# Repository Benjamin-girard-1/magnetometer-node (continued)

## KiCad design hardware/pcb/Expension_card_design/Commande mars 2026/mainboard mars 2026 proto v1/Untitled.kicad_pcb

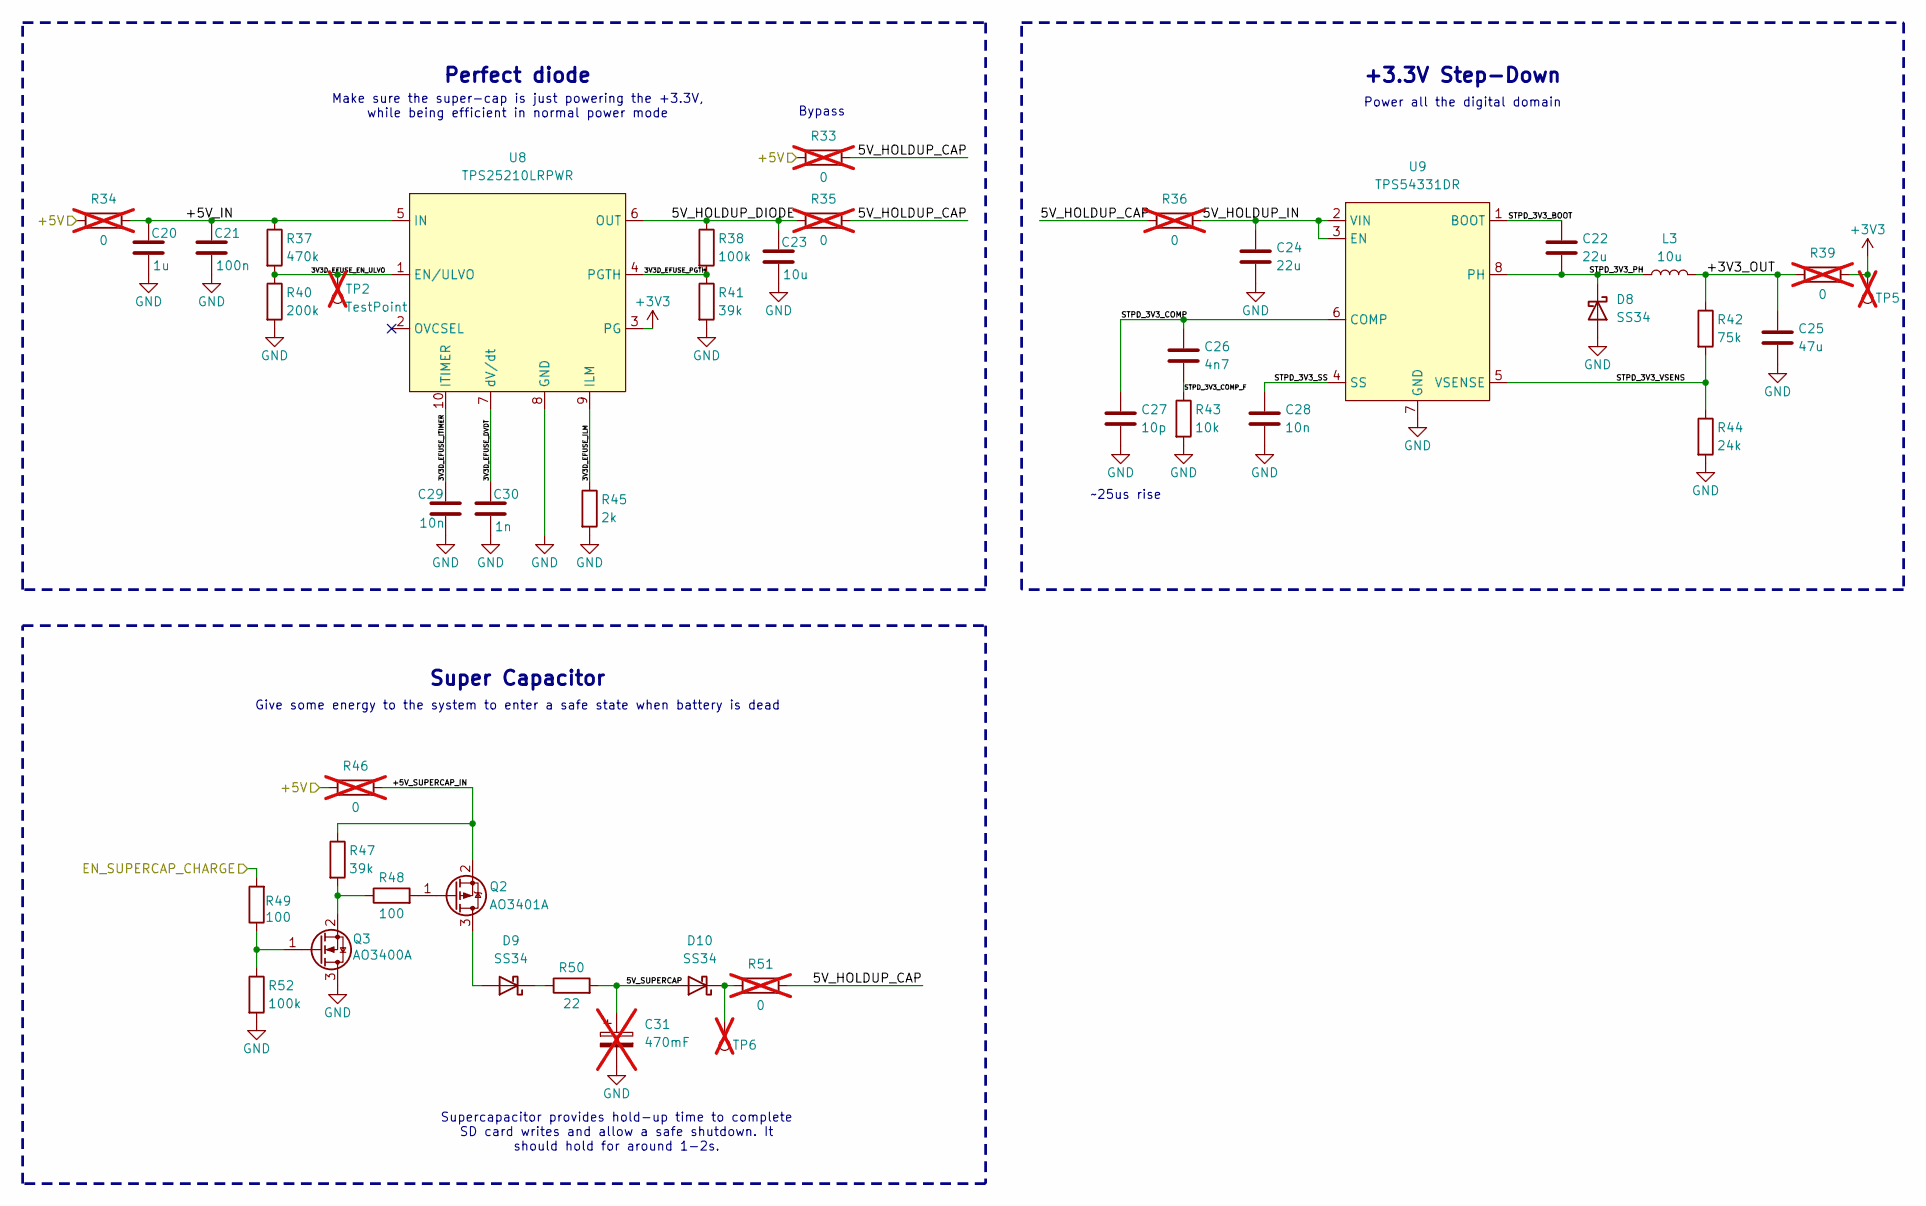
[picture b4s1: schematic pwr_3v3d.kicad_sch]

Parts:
C20: 1u; C_0805_2012Metric; LCSC C28323
C21: 100n; C_0603_1608Metric; LCSC C14663
C22, C24: 22u; C_1206_3216Metric; LCSC C12891
C23: 10u; C_0805_2012Metric; LCSC C15850
C25: 47u; C_1206_3216Metric; LCSC C96123
C26: 4n7; C_0603_1608Metric; LCSC C53987
C27: 10p; C_0603_1608Metric; LCSC C1634
C28, C29: 10n; C_0603_1608Metric; LCSC C57112
C30: 1n; C_0603_1608Metric; LCSC C1588
C31: 470mF; C_Radial_D8.0mm_P11.50mm; not fitted
D8, D9, D10: SS34; D_SMA; LCSC C8678
L3: 10u; L_Sunlord_MWSA0503S; LCSC C177248
Q2: AO3401A; SOT-23; LCSC C15127
Q3: AO3400A; SOT-23; LCSC C20917
R33, R34, R35, R36, R39, R46, R51: 0; R_1206_3216Metric; LCSC C17888; not fitted
R37: 470k; R_0603_1608Metric; LCSC C23178
R38, R52: 100k; R_0603_1608Metric; LCSC C25803
R40: 200k; R_0603_1608Metric; LCSC C25811
R41, R47: 39k; R_0603_1608Metric; LCSC C23153
R42: 75k; R_0603_1608Metric; LCSC C23242
R43: 10k; R_0603_1608Metric; LCSC C25804
R44: 24k; R_0603_1608Metric; LCSC C23352
R45: 2k; R_0603_1608Metric; LCSC C22975
R48, R49: 100; R_0603_1608Metric; LCSC C22775
R50: 22; R_2512_6332Metric; LCSC C2974113
TP2, TP5, TP6: TestPoint; TestPoint_THTPad_1.0x1.0mm_Drill0.5mm; not fitted
U8: TPS25210LRPWR; SMD_VQFN-HR-10; LCSC C2861226
U9: TPS54331DR; SOIC-8_3.9x4.9mm_P1.27mm; LCSC C9865

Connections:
+3V3: R39.2, TP5.1, U8.3 (PG); also elsewhere on the board
+5V: R33.1, R34.1, R46.1; also elsewhere on the board
/MCU_ESP32S3/EN_SUPERCAP_CHARGE: R49.2; also elsewhere on the board
/PWR_3V3D/3V3D_EFUSE_DVDT: C30.1, U8.7 (dV/dt)
/PWR_3V3D/3V3D_EFUSE_EN_ULVO: R37.2, R40.1, TP2.1, U8.1 (EN/ULVO)
/PWR_3V3D/3V3D_EFUSE_ILM: R45.1, U8.9 (ILM)
/PWR_3V3D/3V3D_EFUSE_ITIMER: C29.1, U8.10 (ITIMER)
/PWR_3V3D/3V3D_EFUSE_PGTH: R38.2, R41.1, U8.4 (PGTH)
/PWR_3V3D/5V_HOLDUP_CAP: R33.2, R35.2, R36.1, R51.2
/PWR_3V3D/5V_HOLDUP_DIODE: C23.1, R35.1, R38.1, U8.6 (OUT)
/PWR_3V3D/5V_HOLDUP_IN: C24.1, R36.2, U9.2 (VIN), U9.3 (EN)
/PWR_3V3D/5V_SUPERCAP: C31.1, D10.2 (A), R50.2
/PWR_3V3D/+3V3_OUT: C25.1, L3.2, R39.1, R42.1
/PWR_3V3D/+5V_IN: C20.1, C21.1, R34.2, R37.1, U8.5 (IN)
/PWR_3V3D/+5V_SUPERCAP_IN: Q2.2 (S), R46.2, R47.1
/PWR_3V3D/STPD_3V3_BOOT: C22.1, U9.1 (BOOT)
/PWR_3V3D/STPD_3V3_COMP: C26.1, C27.1, U9.6 (COMP)
/PWR_3V3D/STPD_3V3_COMP_F: C26.2, R43.1
/PWR_3V3D/STPD_3V3_PH: C22.2, D8.1 (K), L3.1, U9.8 (PH)
/PWR_3V3D/STPD_3V3_SS: C28.1, U9.4 (SS)
/PWR_3V3D/STPD_3V3_VSENS: R42.2, R44.1, U9.5 (VSENSE)
GND: C20.2, C21.2, C23.2, C24.2, C25.2, C27.2, C28.2, C29.2, C30.2, C31.2, D8.2 (A), Q3.3 (D), R40.2, R41.2, R43.2, R44.2, R45.2, R52.2, U8.8 (GND), U9.7 (GND); also elsewhere on the board
unnamed: D9.2 (A), Q2.3 (D)
unnamed: D9.1 (K), R50.1
unnamed: D10.1 (K), R51.1, TP6.1
unnamed: Q2.1 (G), R48.2
unnamed: Q3.1 (G), R49.1, R52.1
unnamed: Q3.2 (S), R47.2, R48.1

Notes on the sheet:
Make sure the super-cap is just powering the +3.3V, while being efficient in normal power mode
~25us rise
Super Capacitor
Give some energy to the system to enter a safe state when battery is dead
+3.3V Step-Down
Power all the digital domain
Supercapacitor provides hold-up time to complete SD card writes and allow a safe shutdown. It should hold for around 1-2s.
Bypass
Perfect diode

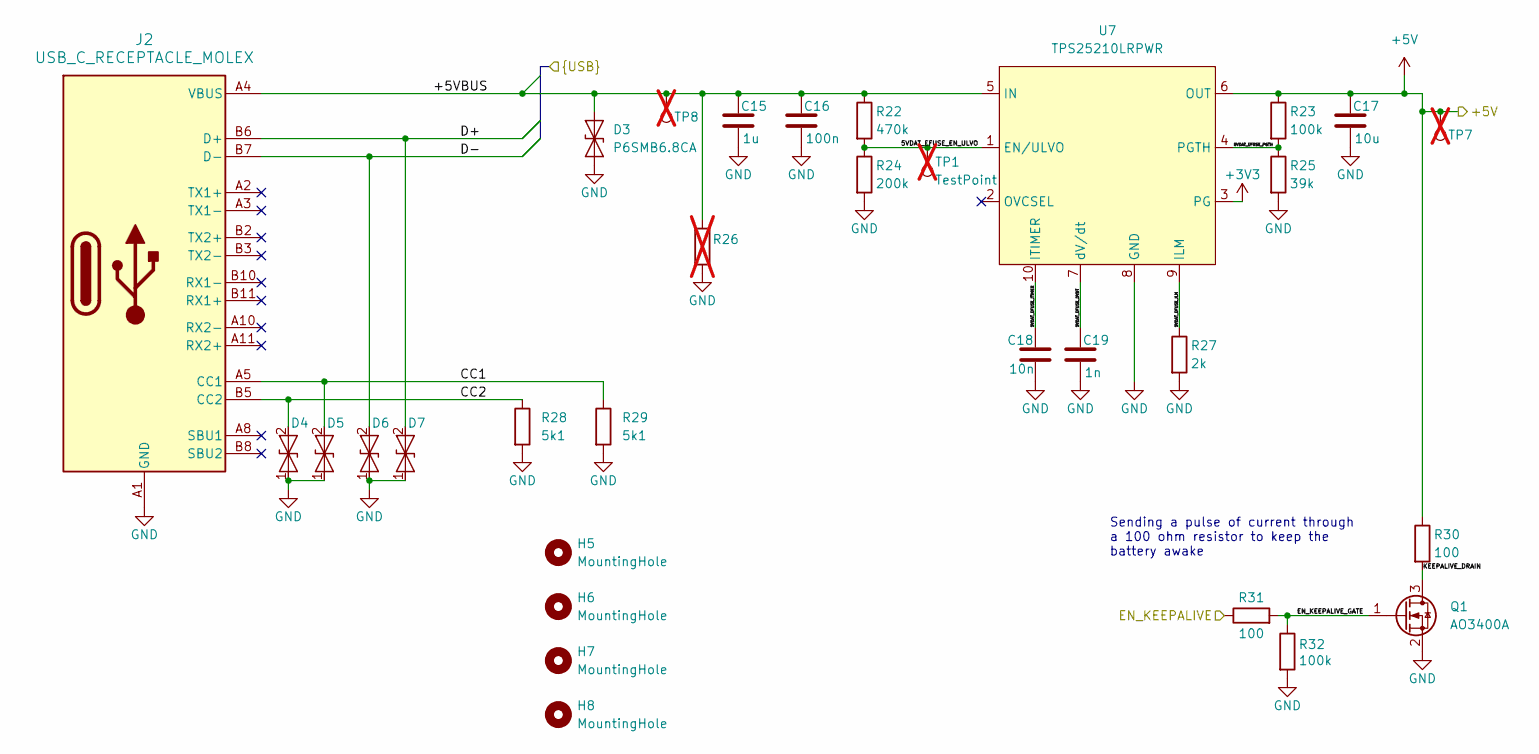
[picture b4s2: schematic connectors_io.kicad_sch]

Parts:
C15: 1u; C_0805_2012Metric; LCSC C28323
C16: 100n; C_0603_1608Metric; LCSC C14663
C17: 10u; C_0805_2012Metric; LCSC C15850
C18: 10n; C_0603_1608Metric; LCSC C57112
C19: 1n; C_0603_1608Metric; LCSC C1588
D3: P6SMB6.8CA; D_SMB; LCSC C7420377
D4, D5, D6, D7: H5VUD5BB; D_SOD-523; LCSC C20615820
H5, H6, H7, H8: MountingHole; MountingHole_4.3mm_M4
J2: USB_C_RECEPTACLE_MOLEX; CONN_201267-0005_MOL; LCSC C565324
Q1: AO3400A; SOT-23; LCSC C20917
R22: 470k; R_0603_1608Metric; LCSC C23178
R23, R32: 100k; R_0603_1608Metric; LCSC C25803
R24: 200k; R_0603_1608Metric; LCSC C25811
R25: 39k; R_0603_1608Metric; LCSC C23153
R26: R_1206_3216Metric_Pad1.30x1.75mm_HandSolder; not fitted
R27: 2k; R_0603_1608Metric; LCSC C22975
R28, R29: 5k1; R_0603_1608Metric; LCSC C23186
R30, R31: 100; R_0603_1608Metric; LCSC C22775
TP1, TP7, TP8: TestPoint; TestPoint_THTPad_1.0x1.0mm_Drill0.5mm; not fitted
U7: TPS25210LRPWR; SMD_VQFN-HR-10; LCSC C2861226

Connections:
+3V3: U7.3 (PG); also elsewhere on the board
+5V: C17.1, R23.1, R30.1, TP7.1, U7.6 (OUT); also elsewhere on the board
/DATA_SAVING/+5VBUS: C15.1, C16.1, D3.2 (A2), J2.A4 (VBUS), J2.A9 (VBUS), J2.B4 (VBUS), J2.B9 (VBUS), R22.1, R26.2, TP8.1, U7.5 (IN); also elsewhere on the board
/DATA_SAVING/CC1: D5.2, J2.A5 (CC1), R29.1
/DATA_SAVING/CC2: D4.2, J2.B5 (CC2), R28.1
/DATA_SAVING/D+: D7.2, J2.A6 (D+), J2.B6 (D+); also elsewhere on the board
/DATA_SAVING/D-: D6.2, J2.A7 (D-), J2.B7 (D-); also elsewhere on the board
/IO_CONNECTOR/5VDAT_EFUSE_DVDT: C19.1, U7.7 (dV/dt)
/IO_CONNECTOR/5VDAT_EFUSE_EN_ULVO: R22.2, R24.1, TP1.1, U7.1 (EN/ULVO)
/IO_CONNECTOR/5VDAT_EFUSE_ILM: R27.1, U7.9 (ILM)
/IO_CONNECTOR/5VDAT_EFUSE_ITIMER: C18.1, U7.10 (ITIMER)
/IO_CONNECTOR/5VDAT_EFUSE_PGTH: R23.2, R25.1, U7.4 (PGTH)
/IO_CONNECTOR/EN_KEEPALIVE: R31.1; also elsewhere on the board
/IO_CONNECTOR/EN_KEEPALIVE_GATE: Q1.1 (G), R31.2, R32.1
/IO_CONNECTOR/KEEPALIVE_DRAIN: Q1.3 (D), R30.2
GND: C15.2, C16.2, C17.2, C18.2, C19.2, D3.1 (A1), D4.1, D5.1, D6.1, D7.1, J2.A1 (GND), J2.A12 (GND), J2.B1 (GND), J2.B12 (GND), Q1.2 (S), R24.2, R25.2, R26.1, R27.2, R28.2, R29.2, R32.2, U7.8 (GND); also elsewhere on the board

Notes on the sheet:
Sending a pulse of current through a 100 ohm resistor to keep the battery awake

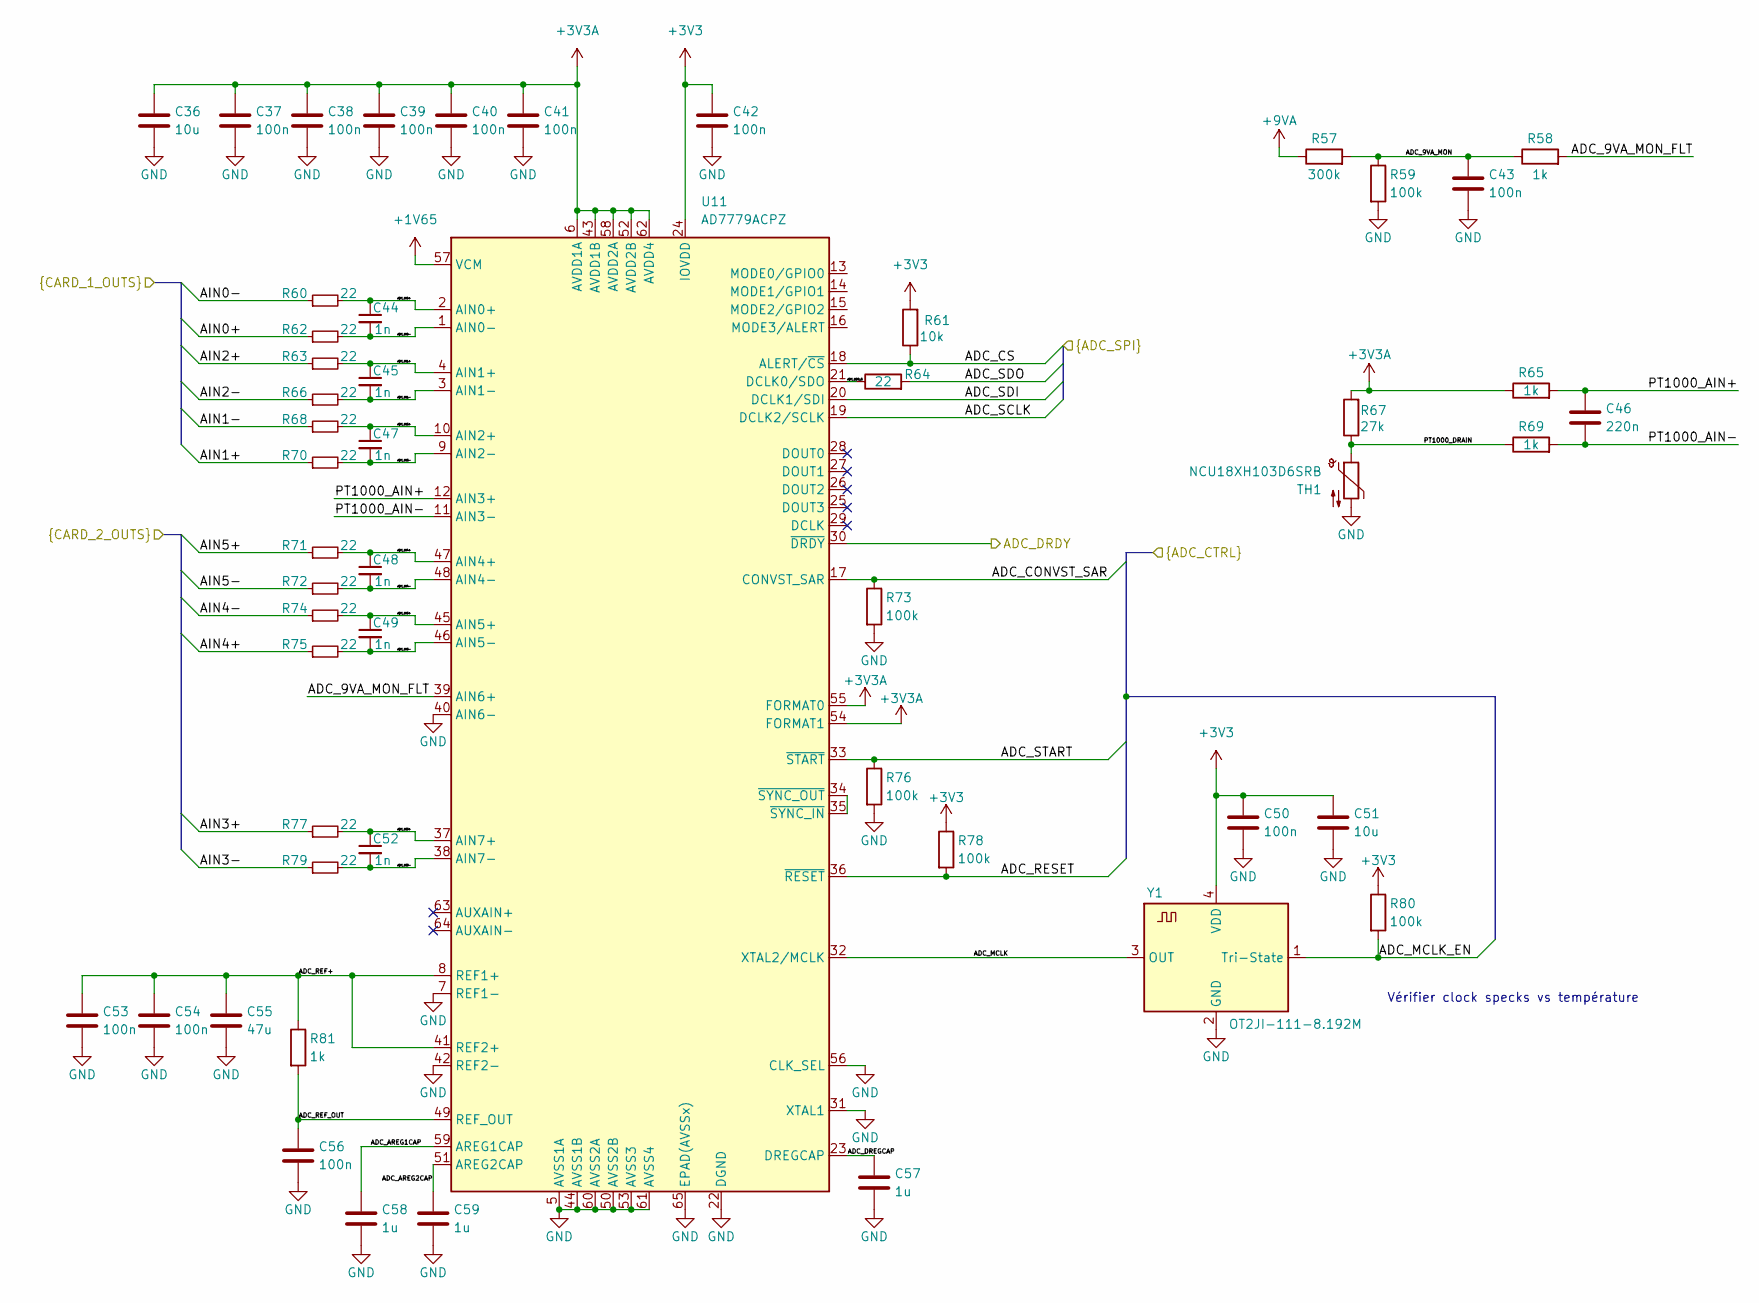
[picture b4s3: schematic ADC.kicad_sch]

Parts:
C36, C51: 10u; C_0805_2012Metric; LCSC C15850
C37, C38, C39, C40, C41, C42, C43, C50, C53, C54, C56: 100n; C_0603_1608Metric; LCSC C14663
C44, C45, C47, C48, C49, C52: 1n; C_0603_1608Metric; LCSC C1588
C46: 220n; C_0603_1608Metric; LCSC C21120
C55: 47u; C_1206_3216Metric; LCSC C96123
C57, C58, C59: 1u; C_0805_2012Metric; LCSC C28323
R57: 300k; R_0603_1608Metric; LCSC C23024
R58, R65, R69, R81: 1k; R_0603_1608Metric; LCSC C21190
R59, R73, R76, R78, R80: 100k; R_0603_1608Metric; LCSC C25803
R60, R62, R63, R64, R66, R68, R70, R71, R72, R74, R75, R77, R79: 22; R_0603_1608Metric; LCSC C23345
R61: 10k; R_0603_1608Metric; LCSC C25804
R67: 27k; R_0805_2012Metric; LCSC C17526
TH1: NCU18XH103D6SRB; R_0603_1608Metric; LCSC C3154835
U11: AD7779ACPZ; QFN-64-1EP_9x9mm_P0.5mm_EP7.65x7.65mm; LCSC C398822
Y1: OT2JI-111-8.192M; Crystal_SMD_3225-4Pin_3.2x2.5mm; LCSC C7425393

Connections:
+1V65: U11.57 (VCM); also elsewhere on the board
+3V3: C42.1, C50.1, C51.1, R61.2, R78.1, R80.1, U11.24 (IOVDD), Y1.4 (VDD); also elsewhere on the board
+3V3A: C36.1, C37.1, C38.1, C39.1, C40.1, C41.1, R65.1, R67.2, U11.6 (AVDD1A), U11.43 (AVDD1B), U11.52 (AVDD2B), U11.54 (FORMAT1), U11.55 (FORMAT0), U11.58 (AVDD2A), U11.62 (AVDD4); also elsewhere on the board
+9VA: R57.1; also elsewhere on the board
/ADC_AD777x/ADC_9VA_MON: C43.1, R57.2, R58.1, R59.1
/ADC_AD777x/ADC_9VA_MON_FLT: R58.2, U11.39 (AIN6+)
/ADC_AD777x/ADC_AREG1CAP: C58.1, U11.59 (AREG1CAP)
/ADC_AD777x/ADC_AREG2CAP: C59.1, U11.51 (AREG2CAP)
/ADC_AD777x/ADC_CONVST_SAR: R73.1, U11.17 (CONVST_SAR); also elsewhere on the board
/ADC_AD777x/ADC_CS: R61.1, U11.18 (ALERT/~CS); also elsewhere on the board
/ADC_AD777x/ADC_DRDY: U11.30 (~DRDY); also elsewhere on the board
/ADC_AD777x/ADC_DREGCAP: C57.1, U11.23 (DREGCAP)
/ADC_AD777x/ADC_IN0+: C44.1, R60.2, U11.2 (AIN0+)
/ADC_AD777x/ADC_IN0-: C44.2, R62.2, U11.1 (AIN0-)
/ADC_AD777x/ADC_IN1+: C45.1, R63.2, U11.4 (AIN1+)
/ADC_AD777x/ADC_IN1-: C45.2, R66.2, U11.3 (AIN1-)
/ADC_AD777x/ADC_IN2+: C47.1, R68.2, U11.10 (AIN2+)
/ADC_AD777x/ADC_IN2-: C47.2, R70.2, U11.9 (AIN2-)
/ADC_AD777x/ADC_IN3+: C52.1, R77.2, U11.37 (AIN7+)
/ADC_AD777x/ADC_IN3-: C52.2, R79.2, U11.38 (AIN7-)
/ADC_AD777x/ADC_IN4+: C48.1, R71.2, U11.47 (AIN4+)
/ADC_AD777x/ADC_IN4-: C48.2, R72.2, U11.48 (AIN4-)
/ADC_AD777x/ADC_IN5+: C49.1, R74.2, U11.45 (AIN5+)
/ADC_AD777x/ADC_IN5-: C49.2, R75.2, U11.46 (AIN5-)
/ADC_AD777x/ADC_MCLK: U11.32 (XTAL2/MCLK), Y1.3 (OUT)
/ADC_AD777x/ADC_MCLK_EN: R80.2, Y1.1 (Tri-State); also elsewhere on the board
/ADC_AD777x/ADC_REF+: C53.1, C54.1, C55.1, R81.1, U11.8 (REF1+), U11.41 (REF2+)
/ADC_AD777x/ADC_REF_OUT: C56.1, R81.2, U11.49 (REF_OUT)
/ADC_AD777x/ADC_RESET: R78.2, U11.36 (~RESET); also elsewhere on the board
/ADC_AD777x/ADC_SCLK: U11.19 (DCLK2/SCLK); also elsewhere on the board
/ADC_AD777x/ADC_SDI: U11.20 (DCLK1/SDI); also elsewhere on the board
/ADC_AD777x/ADC_SDO: R64.2; also elsewhere on the board
/ADC_AD777x/ADC_SDO_R: R64.1, U11.21 (DCLK0/SDO)
/ADC_AD777x/ADC_START: R76.1, U11.33 (~START); also elsewhere on the board
/ADC_AD777x/AIN0+: R62.1; also elsewhere on the board
/ADC_AD777x/AIN0-: R60.1; also elsewhere on the board
/ADC_AD777x/AIN1+: R70.1; also elsewhere on the board
/ADC_AD777x/AIN1-: R68.1; also elsewhere on the board
/ADC_AD777x/AIN2+: R63.1; also elsewhere on the board
/ADC_AD777x/AIN2-: R66.1; also elsewhere on the board
/ADC_AD777x/AIN3+: R77.1; also elsewhere on the board
/ADC_AD777x/AIN3-: R79.1; also elsewhere on the board
/ADC_AD777x/AIN4+: R75.1; also elsewhere on the board
/ADC_AD777x/AIN4-: R74.1; also elsewhere on the board
/ADC_AD777x/AIN5+: R71.1; also elsewhere on the board
/ADC_AD777x/AIN5-: R72.1; also elsewhere on the board
/ADC_AD777x/PT1000_AIN+: C46.1, R65.2, U11.12 (AIN3+)
/ADC_AD777x/PT1000_AIN-: C46.2, R69.2, U11.11 (AIN3-)
/ADC_AD777x/PT1000_DRAIN: R67.1, R69.1, TH1.1
GND: C36.2, C37.2, C38.2, C39.2, C40.2, C41.2, C42.2, C43.2, C50.2, C51.2, C53.2, C54.2, C55.2, C56.2, C57.2, C58.2, C59.2, R59.2, R73.2, R76.2, TH1.2, U11.5 (AVSS1A), U11.7 (REF1-), U11.22 (DGND), U11.31 (XTAL1), U11.40 (AIN6-), U11.42 (REF2-), U11.44 (AVSS1B), U11.50 (AVSS2B), U11.53 (AVSS3), U11.56 (CLK_SEL), U11.60 (AVSS2A), U11.61 (AVSS4), U11.65 (EPAD(AVSSx)), Y1.2 (GND); also elsewhere on the board
unnamed: U11.34 (~SYNC_OUT), U11.35 (~SYNC_IN)

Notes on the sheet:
Vérifier clock specks vs température

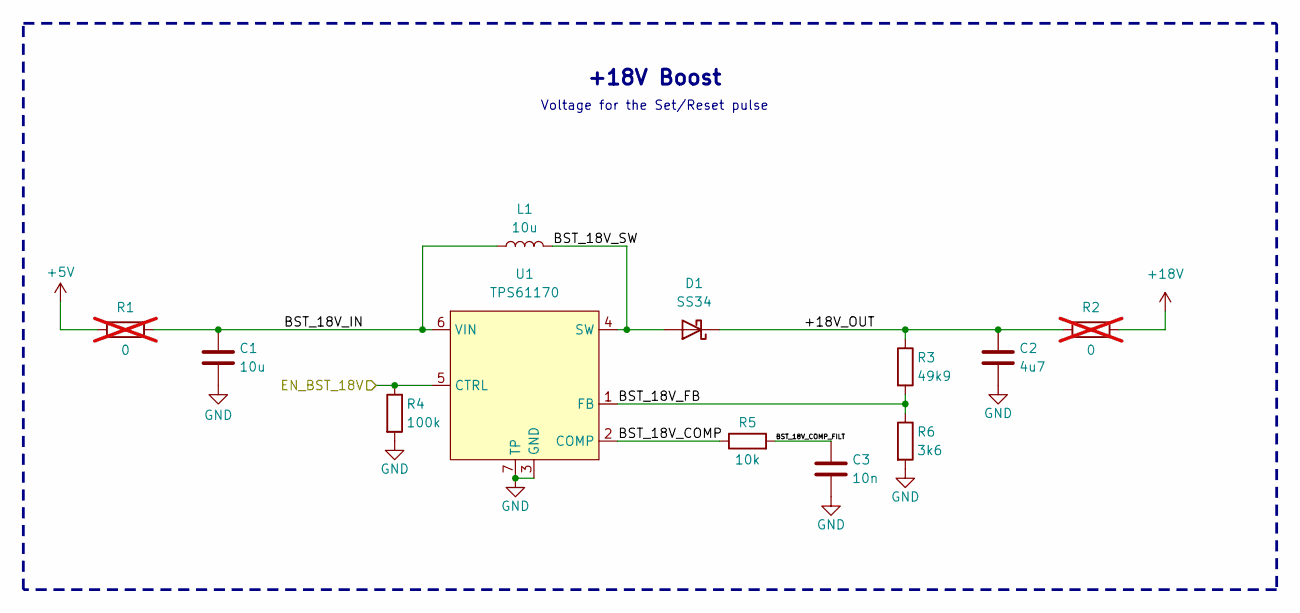
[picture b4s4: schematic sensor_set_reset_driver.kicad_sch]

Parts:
C1: 10u; C_0805_2012Metric; LCSC C15850
C2: 4u7; C_1206_3216Metric; LCSC C29823
C3: 10n; C_0603_1608Metric; LCSC C57112
D1: SS34; D_SMA; LCSC C8678
L1: 10u; L_Sunlord_MWSA0503S; LCSC C177248
R1, R2: 0; R_1206_3216Metric; LCSC C17888; not fitted
R3: 49k9; R_0603_1608Metric; LCSC C23184
R4: 100k; R_0603_1608Metric; LCSC C25803
R5: 10k; R_0603_1608Metric; LCSC C25804
R6: 3k6; R_0603_1608Metric; LCSC C22980
U1: TPS61170; WSON-6-1EP_2x2mm_P0.65mm_EP1x1.6mm; LCSC C15163

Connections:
+5V: R1.1; also elsewhere on the board
+18V: R2.2; also elsewhere on the board
/MCU_ESP32S3/EN_BST_18V: R4.1, U1.5 (CTRL); also elsewhere on the board
/SENSOR_SET_RESET_DRIVER/+18V_OUT: C2.1, D1.1 (K), R2.1, R3.1
/SENSOR_SET_RESET_DRIVER/BST_18V_COMP: R5.1, U1.2 (COMP)
/SENSOR_SET_RESET_DRIVER/BST_18V_COMP_FILT: C3.1, R5.2
/SENSOR_SET_RESET_DRIVER/BST_18V_FB: R3.2, R6.1, U1.1 (FB)
/SENSOR_SET_RESET_DRIVER/BST_18V_IN: C1.1, L1.1, R1.2, U1.6 (VIN)
/SENSOR_SET_RESET_DRIVER/BST_18V_SW: D1.2 (A), L1.2, U1.4 (SW)
GND: C1.2, C2.2, C3.2, R4.2, R6.2, U1.3 (GND), U1.7 (TP); also elsewhere on the board

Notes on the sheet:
+18V Boost
Voltage for the Set/Reset pulse

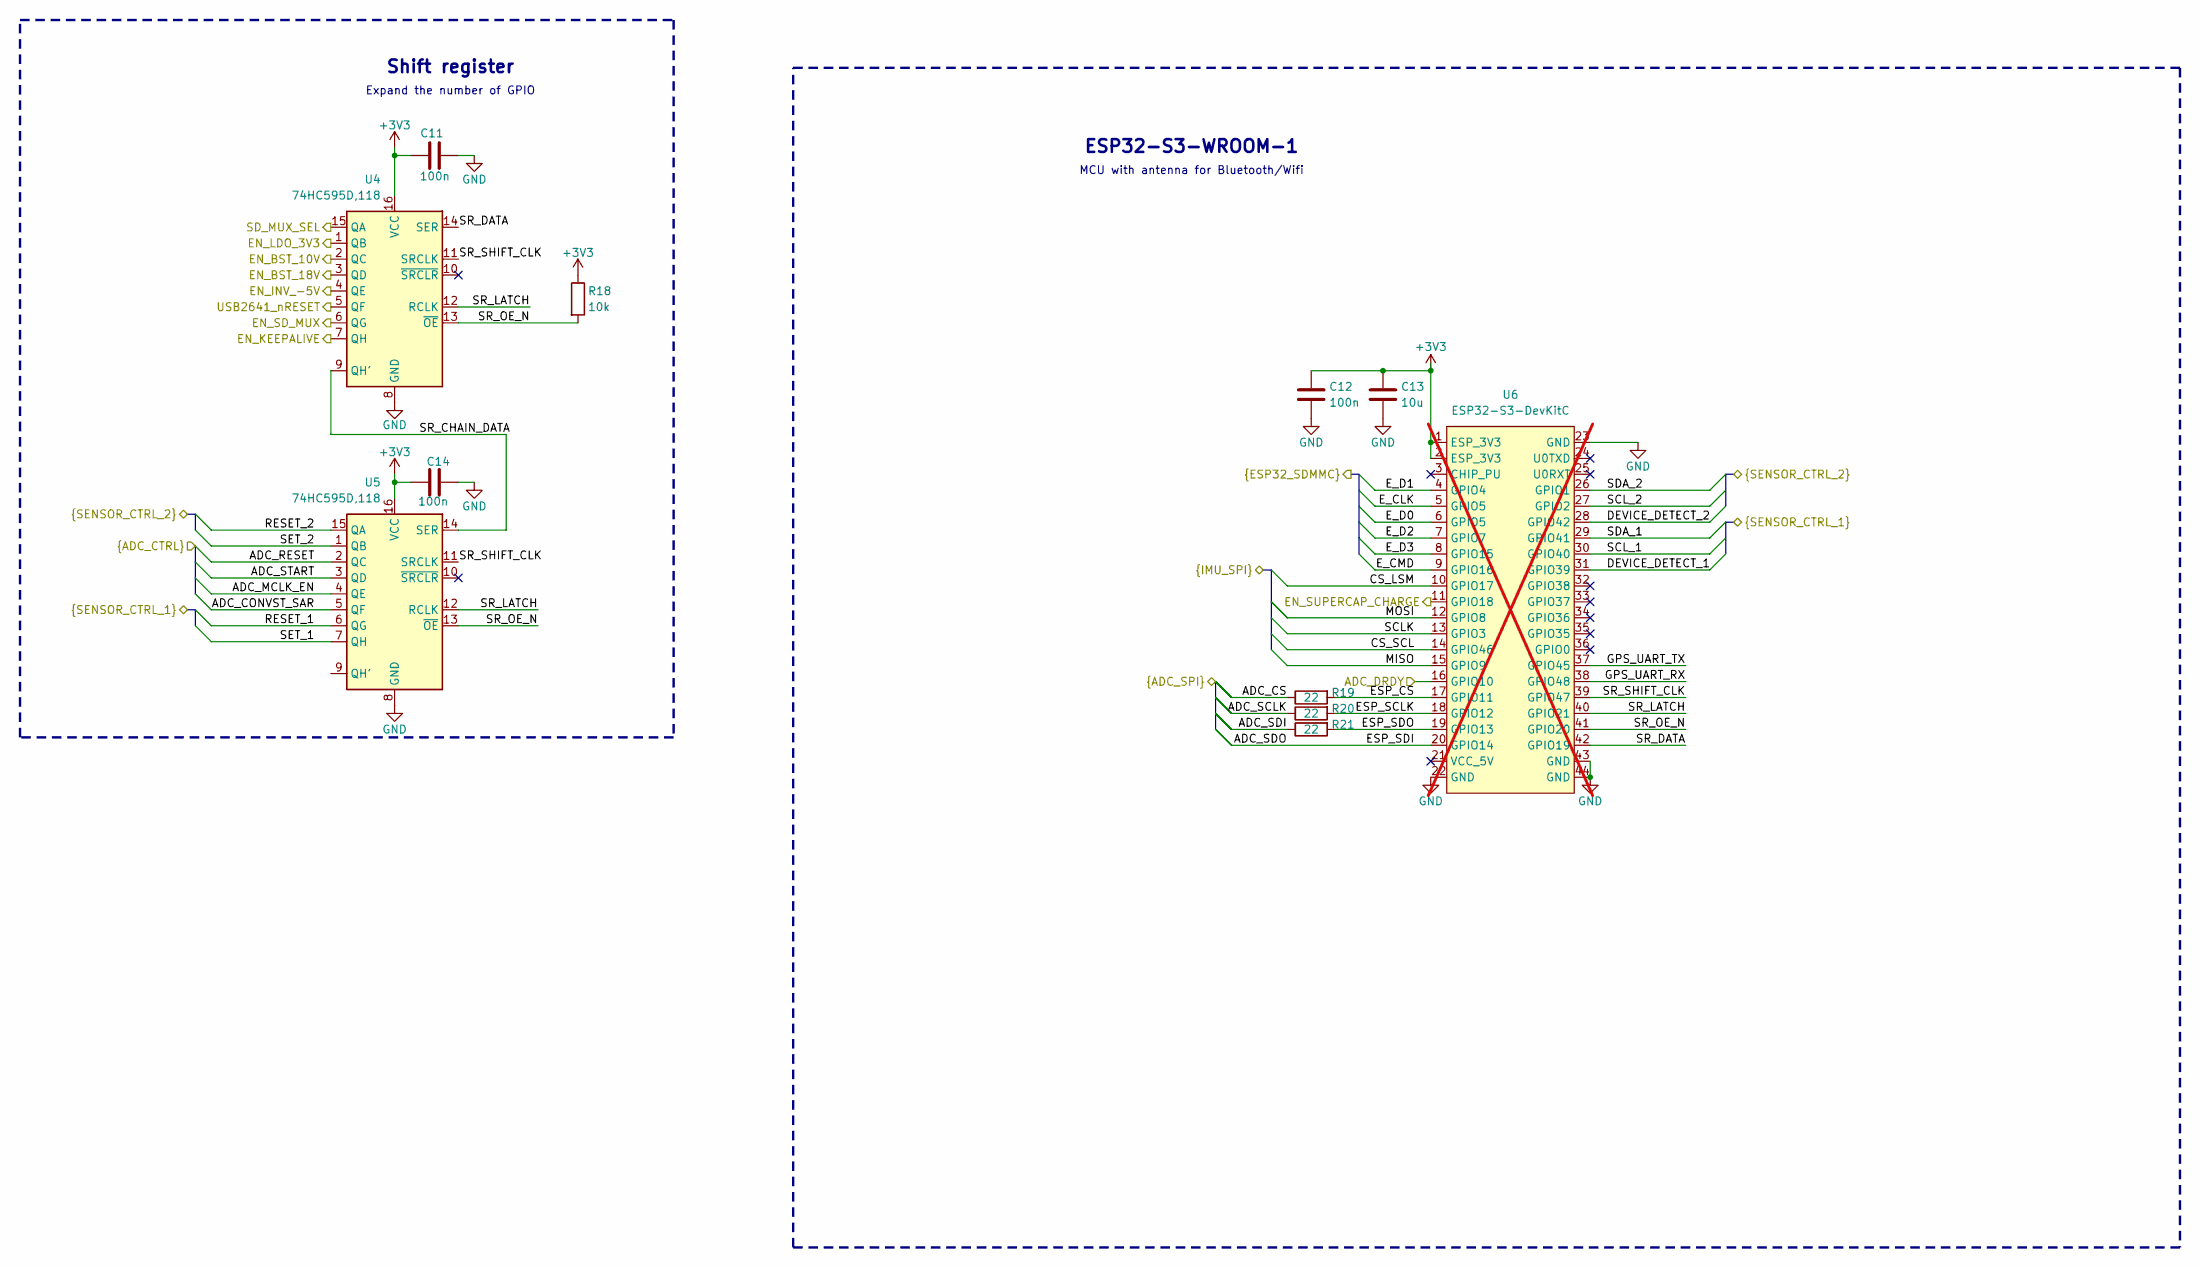
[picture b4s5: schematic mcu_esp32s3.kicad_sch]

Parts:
C11, C12, C14: 100n; C_0603_1608Metric; LCSC C14663
C13: 10u; C_0805_2012Metric; LCSC C15850
R18: 10k; R_0603_1608Metric; LCSC C25804
R19, R20, R21: 22; R_0603_1608Metric; LCSC C23345
U4, U5: 74HC595D,118; SOIC-16_3.9x9.9mm_P1.27mm; LCSC C5947
U6: ESP32-S3-DevKitC; MODULE_ESP32-S3-DEVKITC; not fitted

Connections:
+3V3: C11.1, C12.1, C13.1, C14.1, R18.1, U4.16 (VCC), U5.16 (VCC), U6.1 (ESP_3V3), U6.2 (ESP_3V3); also elsewhere on the board
/ADC_AD777x/ADC_CONVST_SAR: U5.5 (QF); also elsewhere on the board
/ADC_AD777x/ADC_CS: R19.1; also elsewhere on the board
/ADC_AD777x/ADC_DRDY: U6.16 (GPIO10); also elsewhere on the board
/ADC_AD777x/ADC_MCLK_EN: U5.4 (QE); also elsewhere on the board
/ADC_AD777x/ADC_RESET: U5.2 (QC); also elsewhere on the board
/ADC_AD777x/ADC_SCLK: R20.1; also elsewhere on the board
/ADC_AD777x/ADC_SDI: R21.1; also elsewhere on the board
/ADC_AD777x/ADC_SDO: U6.20 (GPIO14); also elsewhere on the board
/ADC_AD777x/ADC_START: U5.3 (QD); also elsewhere on the board
/DATA_SAVING/EN_SD_MUX: U4.6 (QG); also elsewhere on the board
/DATA_SAVING/E_CLK: U6.5 (GPIO5); also elsewhere on the board
/DATA_SAVING/E_CMD: U6.9 (GPIO16); also elsewhere on the board
/DATA_SAVING/E_D0: U6.6 (GPIO5); also elsewhere on the board
/DATA_SAVING/E_D1: U6.4 (GPIO4); also elsewhere on the board
/DATA_SAVING/E_D2: U6.7 (GPIO7); also elsewhere on the board
/DATA_SAVING/E_D3: U6.8 (GPIO15); also elsewhere on the board
/DATA_SAVING/SD_MUX_SEL: U4.15 (QA); also elsewhere on the board
/DATA_SAVING/USB2641_nRESET: U4.5 (QF); also elsewhere on the board
/DEVICE_DETECT_1: U6.31 (GPIO39); also elsewhere on the board
/DEVICE_DETECT_2: U6.28 (GPIO42); also elsewhere on the board
/IMU/CS_LSM: U6.10 (GPIO17); also elsewhere on the board
/IMU/CS_SCL: U6.14 (GPIO46); also elsewhere on the board
/IMU/MISO: U6.15 (GPIO9); also elsewhere on the board
/IMU/MOSI: U6.12 (GPIO8); also elsewhere on the board
/IMU/SCLK: U6.13 (GPIO3); also elsewhere on the board
/IO_CONNECTOR/EN_KEEPALIVE: U4.7 (QH); also elsewhere on the board
/MCU_ESP32S3/EN_BST_10V: U4.2 (QC); also elsewhere on the board
/MCU_ESP32S3/EN_BST_18V: U4.3 (QD); also elsewhere on the board
/MCU_ESP32S3/EN_INV_-5V: U4.4 (QE); also elsewhere on the board
/MCU_ESP32S3/EN_LDO_3V3: U4.1 (QB); also elsewhere on the board
/MCU_ESP32S3/EN_SUPERCAP_CHARGE: U6.11 (GPIO18); also elsewhere on the board
/MCU_ESP32S3/ESP_CS: R19.2, U6.17 (GPIO11)
/MCU_ESP32S3/ESP_SCLK: R20.2, U6.18 (GPIO12)
/MCU_ESP32S3/ESP_SDO: R21.2, U6.19 (GPIO13)
/MCU_ESP32S3/GPS_UART_RX: U6.38 (GPIO48)
/MCU_ESP32S3/GPS_UART_TX: U6.37 (GPIO45)
/MCU_ESP32S3/SR_CHAIN_DATA: U4.9 (QH'), U5.14 (SER)
/MCU_ESP32S3/SR_DATA: U4.14 (SER), U6.42 (GPIO19)
/MCU_ESP32S3/SR_LATCH: U4.12 (RCLK), U5.12 (RCLK), U6.40 (GPIO21)
/MCU_ESP32S3/SR_OE_N: R18.2, U4.13 (~OE), U5.13 (~OE), U6.41 (GPIO20)
/MCU_ESP32S3/SR_SHIFT_CLK: U4.11 (SRCLK), U5.11 (SRCLK), U6.39 (GPIO47)
/RESET_1: U5.6 (QG); also elsewhere on the board
/RESET_2: U5.15 (QA); also elsewhere on the board
/SCL_1: U6.30 (GPIO40); also elsewhere on the board
/SCL_2: U6.27 (GPIO2); also elsewhere on the board
/SDA_1: U6.29 (GPIO41); also elsewhere on the board
/SDA_2: U6.26 (GPIO1); also elsewhere on the board
/SET_1: U5.7 (QH); also elsewhere on the board
/SET_2: U5.1 (QB); also elsewhere on the board
GND: C11.2, C12.2, C13.2, C14.2, U4.8 (GND), U5.8 (GND), U6.22 (GND), U6.23 (GND), U6.43 (GND), U6.44 (GND); also elsewhere on the board

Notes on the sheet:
Shift register
Expand the number of GPIO
ESP32-S3-WROOM-1
MCU with antenna for Bluetooth/Wifi

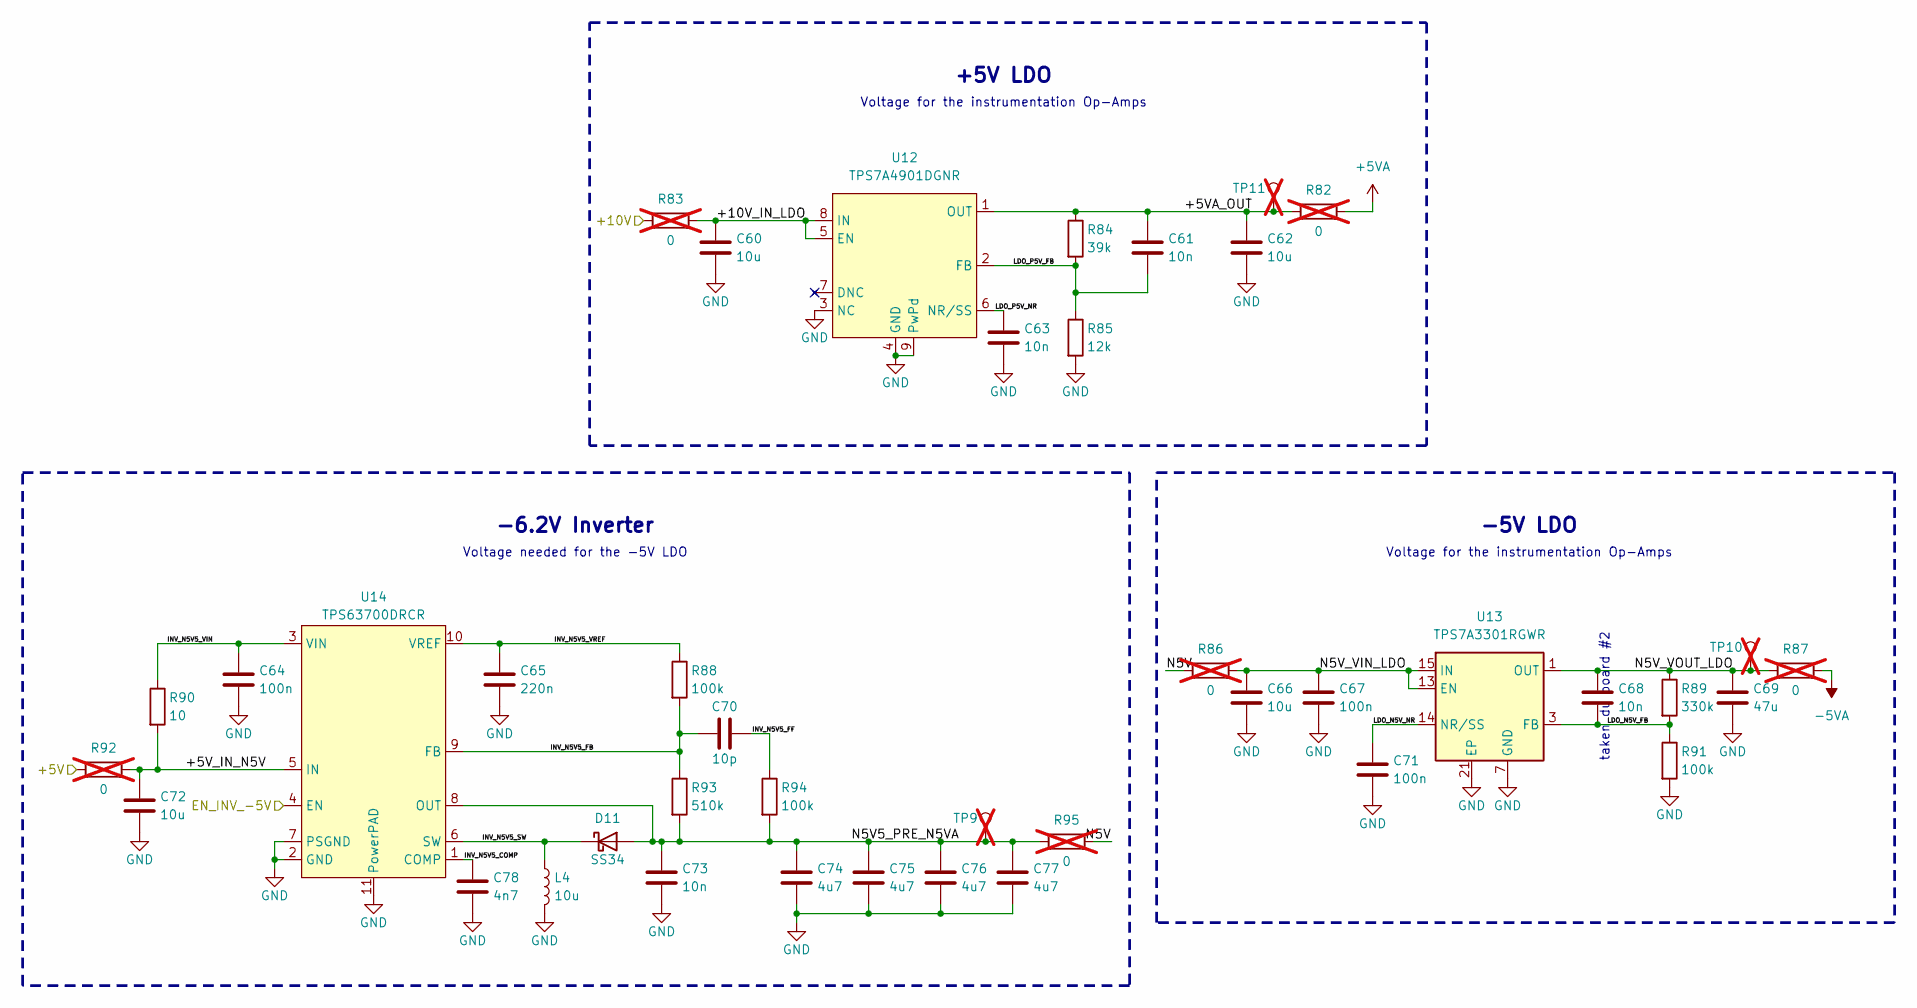
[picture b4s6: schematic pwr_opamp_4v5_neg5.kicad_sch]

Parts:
C60, C62, C66, C72: 10u; C_0805_2012Metric; LCSC C15850
C61, C63, C68, C73: 10n; C_0603_1608Metric; LCSC C57112
C64, C67, C71: 100n; C_0603_1608Metric; LCSC C14663
C65: 220n; C_0603_1608Metric; LCSC C21120
C69: 47u; C_1206_3216Metric; LCSC C96123
C70: 10p; C_0603_1608Metric; LCSC C1634
C74, C75, C76, C77: 4u7; C_1206_3216Metric; LCSC C29823
C78: 4n7; C_0603_1608Metric; LCSC C53987
D11: SS34; D_SMA; LCSC C8678
L4: 10u; L_Sunlord_MWSA0503S; LCSC C177248
R82, R83, R86, R87, R92, R95: 0; R_1206_3216Metric; LCSC C17888; not fitted
R84: 39k; R_0603_1608Metric; LCSC C23153
R85: 12k; R_0603_1608Metric; LCSC C22790
R88, R91, R94: 100k; R_0603_1608Metric; LCSC C25803
R89: 330k; R_0603_1608Metric; LCSC C23137
R90: 10; R_0603_1608Metric; LCSC C22859
R93: 510k; R_0603_1608Metric; LCSC C23192
TP9, TP10, TP11: TestPoint; TestPoint_THTPad_1.0x1.0mm_Drill0.5mm; not fitted
U12: TPS7A4901DGNR; HVSSOP-8-1EP_3x3mm_P0.65mm_EP1.57x1.89mm; LCSC C16430
U13: TPS7A3301RGWR; Texas_RGW0020A_VQFN-20-1EP_5x5mm_P0.65mm_EP3.15x3.15mm; LCSC C90082
U14: TPS63700DRCR; VSON-10-1EP_3x3mm_P0.5mm_EP1.2x2mm; LCSC C54792

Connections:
+5V: R92.1; also elsewhere on the board
+5VA: R82.2; also elsewhere on the board
-5VA: R87.2; also elsewhere on the board
/MCU_ESP32S3/EN_INV_-5V: U14.4 (EN); also elsewhere on the board
/PWR_5VA_NEG5/+5VA_OUT: C61.1, C62.1, R82.1, R84.1, TP11.1, U12.1 (OUT)
/PWR_5VA_NEG5/+5V_IN_N5V: C72.1, R90.2, R92.2, U14.5 (IN)
/PWR_5VA_NEG5/+10V_IN_LDO: C60.1, R83.2, U12.5 (EN), U12.8 (IN)
/PWR_5VA_NEG5/INV_N5V5_COMP: C78.1, U14.1 (COMP)
/PWR_5VA_NEG5/INV_N5V5_FB: C70.1, R88.2, R93.1, U14.9 (FB)
/PWR_5VA_NEG5/INV_N5V5_FF: C70.2, R94.1
/PWR_5VA_NEG5/INV_N5V5_SW: D11.1 (K), L4.1, U14.6 (SW)
/PWR_5VA_NEG5/INV_N5V5_VIN: C64.1, R90.1, U14.3 (VIN)
/PWR_5VA_NEG5/INV_N5V5_VREF: C65.1, R88.1, U14.10 (VREF)
/PWR_5VA_NEG5/LDO_N5V_FB: C68.2, R89.2, R91.1, U13.3 (FB)
/PWR_5VA_NEG5/LDO_N5V_NR: C71.1, U13.14 (NR/SS)
/PWR_5VA_NEG5/LDO_P5V_FB: C61.2, R84.2, R85.1, U12.2 (FB)
/PWR_5VA_NEG5/LDO_P5V_NR: C63.1, U12.6 (NR/SS)
/PWR_5VA_NEG5/N5V: R86.1, R95.2
/PWR_5VA_NEG5/N5V5_PRE_N5VA: C73.1, C74.1, C75.1, C76.1, C77.1, D11.2 (A), R93.2, R94.2, R95.1, TP9.1, U14.8 (OUT)
/PWR_5VA_NEG5/N5V_VIN_LDO: C66.1, C67.1, R86.2, U13.13 (EN), U13.15 (IN), U13.16 (IN)
/PWR_5VA_NEG5/N5V_VOUT_LDO: C68.1, C69.1, R87.1, R89.1, TP10.1, U13.1 (OUT), U13.20 (OUT)
/PWR_9V_BRIDGE/+10V: R83.1; also elsewhere on the board
GND: C60.2, C62.2, C63.2, C64.2, C65.2, C66.2, C67.2, C69.2, C71.2, C72.2, C73.2, C74.2, C75.2, C76.2, C77.2, C78.2, L4.2, R85.2, R91.2, U12.3 (NC), U12.4 (GND), U12.9 (PwPd), U13.7 (GND), U13.21 (EP), U14.2 (GND), U14.7 (PSGND), U14.11 (PowerPAD); also elsewhere on the board

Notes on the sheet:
-5V LDO
Voltage for the instrumentation Op-Amps
taken du board #2
Voltage needed for the -5V LDO
+5V LDO
-6.2V Inverter
